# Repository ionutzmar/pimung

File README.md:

# pimung

Pimung este un player muzical şi un planificator al activităţilor zilnice. Acum poţi controla muzica prin bătăi în masă (ciocăniri).  Mai mult, ai opţiunea de a trimite muzica prin reţeaua locală la o placuţă Raspberry Pi la care sunt conectate boxele. Astfel poţi asculta melodiile la boxele sau la sistemul audio din colţul camerii în timp ce stai în pat cu laptop-ul. La Raspberry Pi mai este conectată şi o matrice de leduri pe care se arată frecvenţele melodiei în timp real.
Pimung te şi ajută să fii mai productiv.  Introduci care este scopul tău principal pentru ziua respectivă, iar el îţi reaminteşte mereu in acea zi ce trebuie să faci. Apăsând pe butonul ,,Planner” îţi poţi alcătui un to do list offline. Dacă cumva nu eşti destul de motivat pentru a face ceea ce ţi-ai propus, apasă pe butonul de sub întrebarea ,Need some motivation? şi vei citi un citat motivaţional.

Documentation: https://github.com/ionutzmar/pimung/blob/master/Documentatie/PimungDocumentatie.pdf
Poster: https://github.com/ionutzmar/pimung/blob/master/poster.jpg

The MIT License (MIT)
Copyright (c) <2015> <Ionut Marius Mihalache>

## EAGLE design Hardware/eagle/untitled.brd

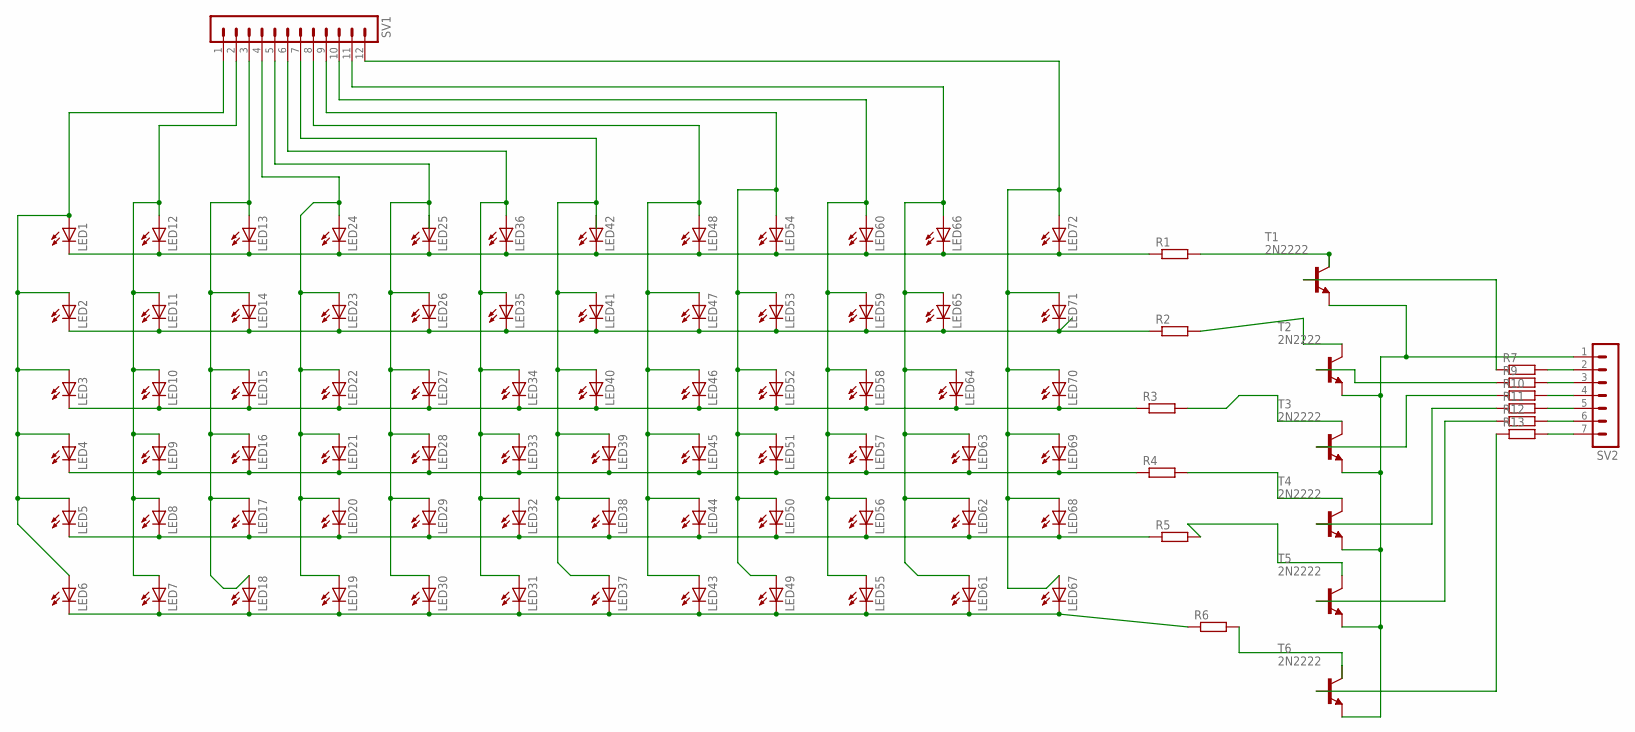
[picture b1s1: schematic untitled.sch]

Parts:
LED1, LED2, LED3, LED4, LED5, LED6, LED7, LED8, LED9, LED10, LED11, LED12, LED13, LED14, LED15, LED16, LED17, LED18, LED19, LED20, LED21, LED22, LED23, LED24, LED25, LED26, LED27, LED28, LED29, LED30, LED31, LED32, LED33, LED34, LED35, LED36, LED37, LED38, LED39, LED40, LED41, LED42, LED43, LED44, LED45, LED46, LED47, LED48, LED49, LED50, LED51, LED52, LED53, LED54, LED55, LED56, LED57, LED58, LED59, LED60, LED61, LED62, LED63, LED64, LED65, LED66, LED67, LED68, LED69, LED70, LED71, LED72: LED5MM
R1, R2, R3, R4, R5, R6, R7, R9, R10, R11, R12, R13: R-EU_0207/10; 0207/10
SV1: MA12-1
SV2: MA07-1
T1, T2, T3, T4, T5, T6: 2N2222; TO18

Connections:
unnamed: R1.2, T1.3 (C)
unnamed: LED1.K (C), LED12.K (C), LED13.K (C), LED24.K (C), LED25.K (C), LED36.K (C), LED42.K (C), LED48.K (C), LED54.K (C), LED60.K (C), LED66.K (C), LED72.K (C), R1.1
unnamed: LED2.K (C), LED11.K (C), LED14.K (C), LED23.K (C), LED26.K (C), LED35.K (C), LED41.K (C), LED47.K (C), LED53.K (C), LED59.K (C), LED65.K (C), LED71.K (C), R2.1
unnamed: R2.2, T2.3 (C)
unnamed: R3.2, T3.3 (C)
unnamed: R4.2, T4.3 (C)
unnamed: LED3.K (C), LED10.K (C), LED15.K (C), LED22.K (C), LED27.K (C), LED34.K (C), LED40.K (C), LED46.K (C), LED52.K (C), LED58.K (C), LED64.K (C), LED70.K (C), R3.1
unnamed: R5.2, T5.3 (C)
unnamed: R6.2, T6.3 (C)
unnamed: LED4.K (C), LED9.K (C), LED16.K (C), LED21.K (C), LED28.K (C), LED33.K (C), LED39.K (C), LED45.K (C), LED51.K (C), LED57.K (C), LED63.K (C), LED69.K (C), R4.1
unnamed: LED7.A, LED8.A, LED9.A, LED10.A, LED11.A, LED12.A, SV1.2
unnamed: LED13.A, LED14.A, LED15.A, LED16.A, LED17.A, LED18.A, SV1.3
unnamed: LED19.A, LED20.A, LED21.A, LED22.A, LED23.A, LED24.A, SV1.4
unnamed: LED25.A, LED26.A, LED27.A, LED28.A, LED29.A, LED30.A, SV1.5
unnamed: LED31.A, LED32.A, LED33.A, LED34.A, LED35.A, LED36.A, SV1.6
unnamed: LED37.A, LED38.A, LED39.A, LED40.A, LED41.A, LED42.A, SV1.7
unnamed: LED43.A, LED44.A, LED45.A, LED46.A, LED47.A, LED48.A, SV1.8
unnamed: LED49.A, LED50.A, LED51.A, LED52.A, LED53.A, LED54.A, SV1.9
unnamed: LED55.A, LED56.A, LED57.A, LED58.A, LED59.A, LED60.A, SV1.10
unnamed: LED61.A, LED62.A, LED63.A, LED64.A, LED65.A, LED66.A, SV1.11
unnamed: LED67.A, LED68.A, LED69.A, LED70.A, LED71.A, LED72.A, SV1.12
unnamed: SV2.1, T1.1 (E), T2.1 (E), T3.1 (E), T4.1 (E), T5.1 (E), T6.1 (E)
unnamed: LED1.A, LED2.A, LED3.A, LED4.A, LED5.A, LED6.A, SV1.1
unnamed: LED5.K (C), LED8.K (C), LED17.K (C), LED20.K (C), LED29.K (C), LED32.K (C), LED38.K (C), LED44.K (C), LED50.K (C), LED56.K (C), LED62.K (C), LED68.K (C), R5.1
unnamed: R7.1, T1.2 (B)
unnamed: R7.2, SV2.2
unnamed: LED6.K (C), LED7.K (C), LED18.K (C), LED19.K (C), LED30.K (C), LED31.K (C), LED37.K (C), LED43.K (C), LED49.K (C), LED55.K (C), LED61.K (C), LED67.K (C), R6.1
unnamed: R9.1, T2.2 (B)
unnamed: R9.2, SV2.3
unnamed: R10.2, SV2.4
unnamed: R11.2, SV2.5
unnamed: R12.2, SV2.6
unnamed: R11.1, T4.2 (B)
unnamed: R13.2, SV2.7
unnamed: R10.1, T3.2 (B)
unnamed: R12.1, T5.2 (B)
unnamed: R13.1, T6.2 (B)

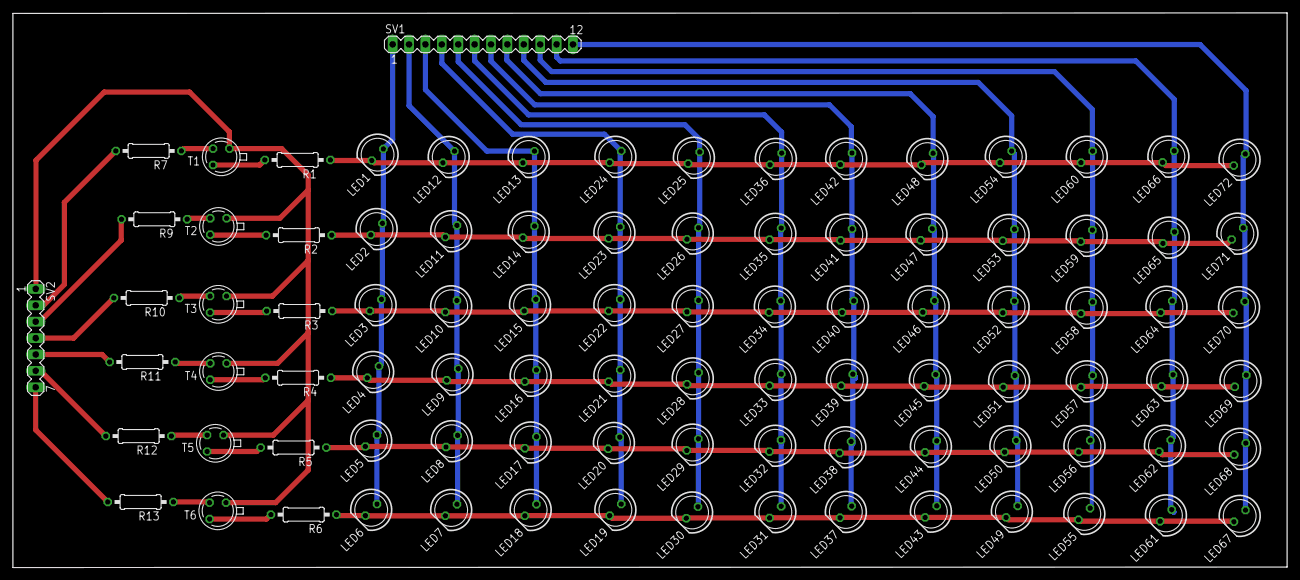
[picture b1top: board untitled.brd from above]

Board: 2 copper layers, 197.5 x 86.0 mm, 92 parts (0 on the bottom side), 37 nets.

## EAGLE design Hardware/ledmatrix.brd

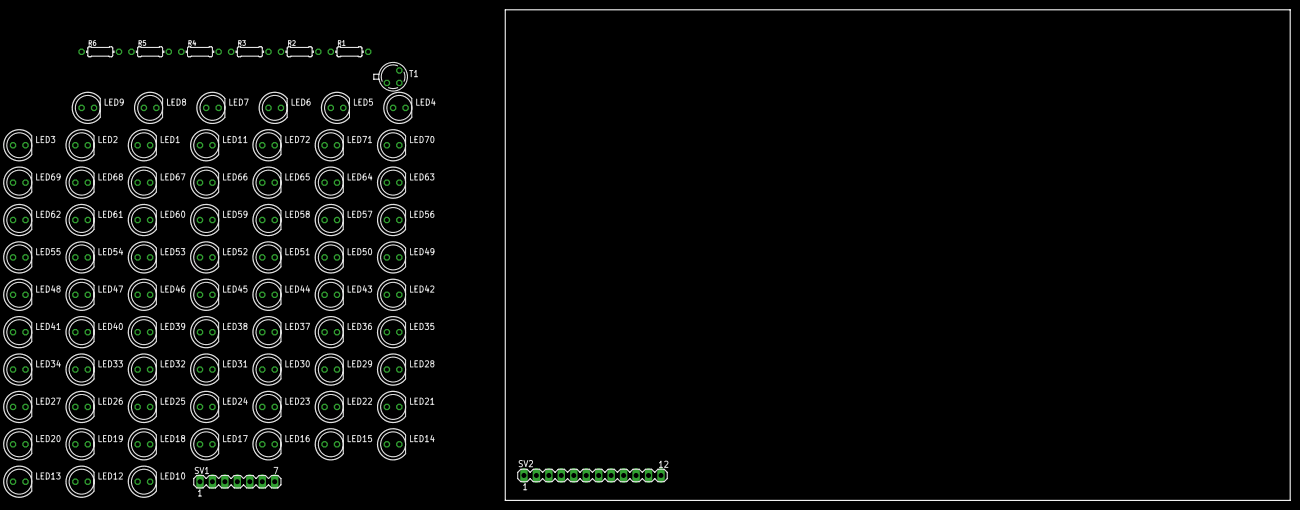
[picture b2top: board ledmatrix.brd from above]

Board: 2 copper layers, 160.0 x 100.0 mm, 81 parts (0 on the bottom side), 2 nets, no tracks yet.

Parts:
LED1, LED2, LED3, LED4, LED5, LED6, LED7, LED8, LED9, LED10, LED11, LED12, LED13, LED14, LED15, LED16, LED17, LED18, LED19, LED20, LED21, LED22, LED23, LED24, LED25, LED26, LED27, LED28, LED29, LED30, LED31, LED32, LED33, LED34, LED35, LED36, LED37, LED38, LED39, LED40, LED41, LED42, LED43, LED44, LED45, LED46, LED47, LED48, LED49, LED50, LED51, LED52, LED53, LED54, LED55, LED56, LED57, LED58, LED59, LED60, LED61, LED62, LED63, LED64, LED65, LED66, LED67, LED68, LED69, LED70, LED71, LED72: LED5MM
R1, R2, R3, R4, R5, R6: 0204/7
SV1: MA07-1
SV2: MA12-1
T1: 2N2222; TO18

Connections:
unnamed: LED12.K, LED13.K, LED36.K, LED37.K, LED60.K, LED61.K, T1.3
unnamed: LED11.K, LED14.K, LED35.K, LED38.K, LED59.K, LED62.K

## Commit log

2015-07-01 Beginning
2015-07-01 First step
2015-07-02 asdf
2015-07-02 qwer
2015-07-02 Resize working properly
2015-07-02 Design
2015-07-03 Design added
2015-07-03 Background color added
2015-07-06 Buttons added
2015-07-06 hardware added
2015-07-07 Huge things
2015-07-07 More working
2015-07-08 t6yu
2015-07-08 adding music to library
2015-07-09 work
2015-07-13 hhsdfg
2015-07-14 zxcv
2015-07-15 Some working
2015-07-16 almost done
2015-07-20 some work
2015-07-22 weryiop
2015-07-22 eagle restart
2015-07-22 with eagle
2015-07-23 with matrix
2015-07-26 working
2015-07-26 license
2015-07-26 eagle files deleted
2015-07-26 htedg
2015-07-27 knocks
2015-07-28 Almost
2015-07-28 Cu documentatie
2015-07-29 dfghj
2015-07-30 ouhouh
2015-07-30 errors solved
2015-07-30 Readme updated
2015-07-30 Documentatie revizuita
2015-07-30 Cleaning
2015-07-31 wav solved
2015-07-31 ready
2015-07-31 hmmmm
2015-07-31 another
2015-07-31 hope
2015-07-31 last
2015-07-31 ultimate
2015-07-31 ultimate try
2015-07-31 With gitignore
2015-07-31 With raspberry
2015-07-31 get ready
2015-07-31 With scheme
